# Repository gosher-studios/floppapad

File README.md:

silly little macropad

### features
- 10 hotswappable mx switches
- 128x32px oled display
- rotary encoder
- usb c
- scriptable and extensible firmware (coming soon)
- the silly caracal
<br/><br/><br/>

### Parts list

| Part                             | Quantity | Est. price | Example link |
|----------------------------------|----------|------------|--------------|
| RP2040                           | 1        | $1.01      | [LCSC](https://www.lcsc.com/product-detail/Microcontroller-Units-MCUs-MPUs-SOCs_Raspberry-Pi-RP2040_C2040.html) |
| USB-C port                       | 1        | $0.16      | [LCSC](https://www.lcsc.com/product-detail/USB-Connectors_Korean-Hroparts-Elec-TYPE-C-31-M-12_C165948.html) |
| SSD1306 128x32 OLED board        | 1        | $4.00      | [42. Keebs](https://42keebs.eu/shop/parts/oled-display-0-91-128x32) |
| EC11 Rotary encoder              | 1        | $2.00      | [LCSC](https://www.lcsc.com/product-detail/span-style-background-color-ff0-Rotary-span-Encoders_ALPSALPINE-EC11E183440C_C370986.html) |
| Kailh MX Hotswap sockets         | 10       | $3.00      | [Mechboards](https://mechboards.co.uk/collections/components/products/kailh-hotswap-sockets) |
| MX Compatible switches           | 10       | ~$10.00    | bring your favourite ✨ |
| SOIC 208-mil SPI flash[^1]       | 1        | $0.56      | [LCSC](https://www.lcsc.com/product-detail/NOR-FLASH_Winbond-Elec-W25Q128JVSIQ_C97521.html) |
| SMD3225 12MHz Crystal oscillator | 1        | $0.06      | [LCSC](https://www.lcsc.com/product-detail/Crystals_YXC-X322512MSB4SI_C9002.html) |
| 3.9x2.9mm SMD Switch             | 1        | $0.11      | [LCSC](https://www.lcsc.com/product-detail/Tactile-Switches_ALPSALPINE-SKRKAEE020_C115357.html) |
| SOT-89 3.3v Voltage regulator    | 1        | $0.05      | [LCSC](https://www.lcsc.com/product-detail/Linear-Voltage-Regulators-LDO_UMW-Youtai-Semiconductor-Co-Ltd-AMS1117-3-3_C347256.html) |
| 27.4Ω Resistors[^2]              | 2        | < $0.00    | [LCSC](https://www.lcsc.com/product-detail/Chip-Resistor-Surface-Mount_UNI-ROYAL-Uniroyal-Elec-0402WGF274JTCE_C31439.html) |
| 1kΩ Resistors[^2]                | 2        | < $0.00    | [LCSC](https://www.lcsc.com/product-detail/Chip-Resistor-Surface-Mount_UNI-ROYAL-Uniroyal-Elec-0402WGF1001TCE_C11702.html) |
| 5.1kΩ Resistors[^2]              | 2        | < $0.00    | [LCSC](https://www.lcsc.com/product-detail/Chip-Resistor-Surface-Mount_UNI-ROYAL-Uniroyal-Elec-0402WGF5101TCE_C25905.html) |
| 27pF Capacitors[^2]              | 2        | < $0.00    | [LCSC](https://www.lcsc.com/product-detail/Multilayer-Ceramic-Capacitors-MLCC-SMD-SMT_Samsung-Electro-Mechanics-CL05C270JB51PNC_C472451.html) |
| 100nF Capacitors[^2]             | 10       | < $0.00    | [LCSC](https://www.lcsc.com/product-detail/Multilayer-Ceramic-Capacitors-MLCC-SMD-SMT_Samsung-Electro-Mechanics-CL05B104KO5NNNC_C1525.html) |
| 1uF Capacitors[^2]               | 2        | < $0.00    | [LCSC](https://www.lcsc.com/product-detail/Multilayer-Ceramic-Capacitors-MLCC-SMD-SMT_Samsung-Electro-Mechanics-CL05A105KA5NQNC_C52923.html) |
| 10uF Capacitors[^2]              | 2        | < $0.00    | [LCSC](https://www.lcsc.com/product-detail/Multilayer-Ceramic-Capacitors-MLCC-SMD-SMT_Samsung-Electro-Mechanics-CL05A106MQ5NUNC_C15525.html) |

[^1]: The firmware is ~36KB for a release build. We use 16MB flash.
[^2]: All resistors and capacitors are 0402.

### Credits

Brought to you by Alex T and Gosha T ❤️ \
This work is licensed under [Creative Commons BY-NC-SA 4.0](https://creativecommons.org/licenses/by-nc-sa/4.0/)

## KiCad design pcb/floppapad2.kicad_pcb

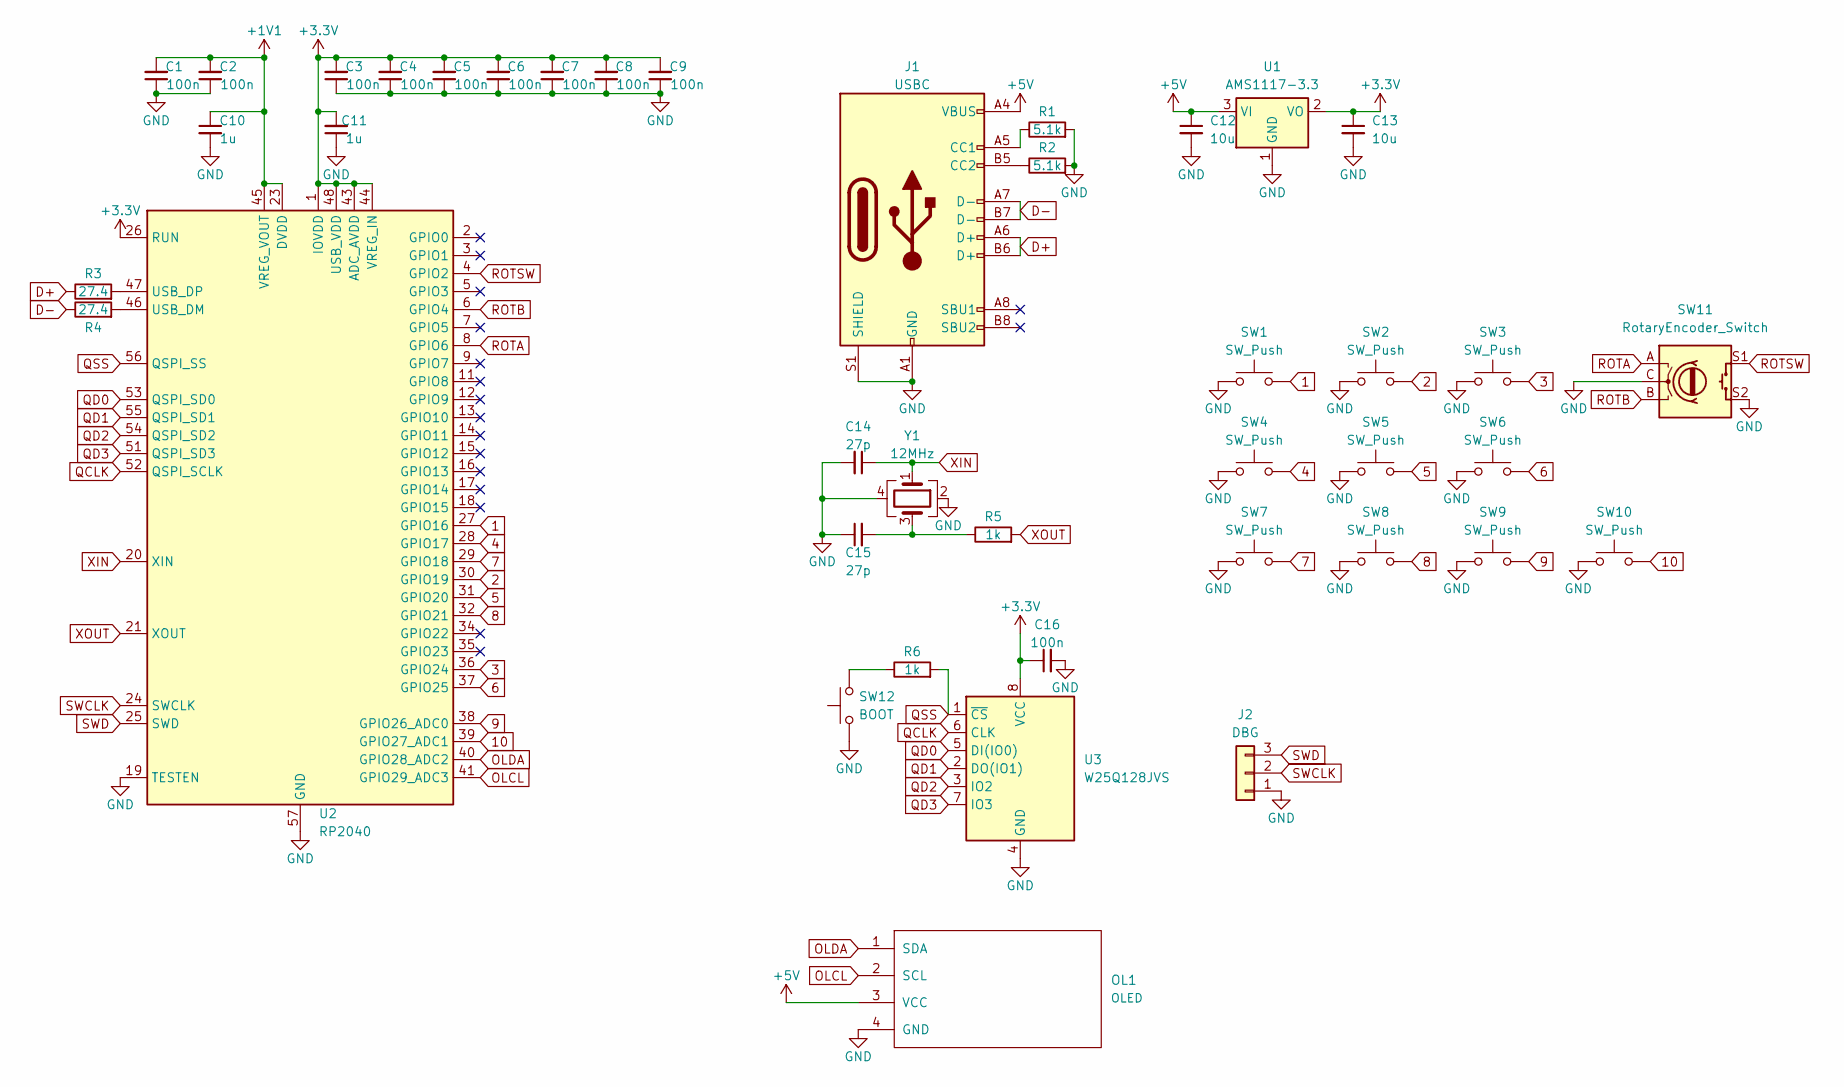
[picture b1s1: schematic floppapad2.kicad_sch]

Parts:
C1, C2, C3, C4, C5, C6, C7, C8, C9, C16: 100n; C_0402_1005Metric
C10, C11: 1u; C_0402_1005Metric
C12, C13: 10u; C_0402_1005Metric
C14, C15: 27p; C_0402_1005Metric
J1: USBC; USB_C_Receptacle_HRO_TYPE-C-31-M-12
J2: DBG; PinSocket_1x03_P2.54mm_Vertical
OL1: OLED; OLED_v2.1
R1, R2: 5.1k; R_0402_1005Metric
R3, R4: 27.4; R_0402_1005Metric
R5, R6: 1k; R_0402_1005Metric
SW1, SW2, SW3, SW4, SW5, SW6, SW7, SW8, SW9, SW10: SW_Push; SW_Hotswap_Kailh_MX_1.00u
SW11: RotaryEncoder_Switch; RotaryEncoder_Alps_EC11E-Switch_Vertical_H20mm
SW12: BOOT; SW_Push_SPST_NO_Alps_SKRK
U1: AMS1117-3.3; SOT-89-3
U2: RP2040; QFN-56-1EP_7x7mm_P0.4mm_EP3.2x3.2mm
U3: W25Q128JVS; SOIC-8_5.23x5.23mm_P1.27mm
Y1: 12MHz; Crystal_SMD_TXC_7M-4Pin_3.2x2.5mm

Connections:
1: SW1.2, U2.27 (GPIO16)
2: SW2.2, U2.30 (GPIO19)
3: SW3.2, U2.36 (GPIO24)
4: SW4.2, U2.28 (GPIO17)
5: SW5.2, U2.31 (GPIO20)
6: SW6.2, U2.37 (GPIO25)
7: SW7.2, U2.29 (GPIO18)
8: SW8.2, U2.32 (GPIO21)
9: SW9.2, U2.38 (GPIO26_ADC0)
10: SW10.2, U2.39 (GPIO27_ADC1)
+1V1: C1.2, C2.2, C10.1, U2.23 (DVDD), U2.45 (VREG_VOUT), U2.50 (DVDD)
+3.3V: C3.2, C4.2, C5.2, C6.2, C7.2, C8.2, C9.2, C11.2, C13.1, C16.1, U1.2 (VO), U2.1 (IOVDD), U2.10 (IOVDD), U2.22 (IOVDD), U2.26 (RUN), U2.33 (IOVDD), U2.42 (IOVDD), U2.43 (ADC_AVDD), U2.44 (VREG_IN), U2.48 (USB_VDD), U2.49 (IOVDD), U3.8 (VCC)
+5V: C12.1, J1.A4 (VBUS), J1.A9 (VBUS), J1.B4 (VBUS), J1.B9 (VBUS), OL1.3 (VCC), U1.3 (VI)
D+: J1.A6 (D+), J1.B6 (D+), R3.1
D-: J1.A7 (D-), J1.B7 (D-), R4.1
GND: C1.1, C2.1, C3.1, C4.1, C5.1, C6.1, C7.1, C8.1, C9.1, C10.2, C11.1, C12.2, C13.2, C14.2, C15.1, C16.2, J1.A1 (GND), J1.A12 (GND), J1.B1 (GND), J1.B12 (GND), J1.S1 (SHIELD), J2.1, OL1.4 (GND), R1.2, R2.2, SW1.1, SW2.1, SW3.1, SW4.1, SW5.1, SW6.1, SW7.1, SW8.1, SW9.1, SW10.1, SW11.C, SW11.S2, SW12.1, SW12.C, SW12.S2, U1.1 (GND), U2.19 (TESTEN), U2.57 (GND), U3.4 (GND), Y1.2, Y1.4; also elsewhere on the board
unnamed: C15.2, R5.1, Y1.3
unnamed: J1.A5 (CC1), R1.1
unnamed: J1.B5 (CC2), R2.1
unnamed: R6.1, SW12.2
unnamed: R4.2, U2.46 (USB_DM)
unnamed: R3.2, U2.47 (USB_DP)
OLCL: OL1.2 (SCL), U2.41 (GPIO29_ADC3)
OLDA: OL1.1 (SDA), U2.40 (GPIO28_ADC2)
QCLK: U2.52 (QSPI_SCLK), U3.6 (CLK)
QD0: U2.53 (QSPI_SD0), U3.5 (DI(IO0))
QD1: U2.55 (QSPI_SD1), U3.2 (DO(IO1))
QD2: U2.54 (QSPI_SD2), U3.3 (IO2)
QD3: U2.51 (QSPI_SD3), U3.7 (IO3)
QSS: R6.2, U2.56 (QSPI_SS), U3.1 (~CS)
ROTA: SW11.A, U2.8 (GPIO6)
ROTB: SW11.B, U2.6 (GPIO4)
ROTSW: SW11.S1, U2.4 (GPIO2)
SWCLK: J2.2, U2.24 (SWCLK); also elsewhere on the board
SWD: J2.3, U2.25 (SWD); also elsewhere on the board
XIN: C14.1, U2.20 (XIN), Y1.1
XOUT: R5.2, U2.21 (XOUT)

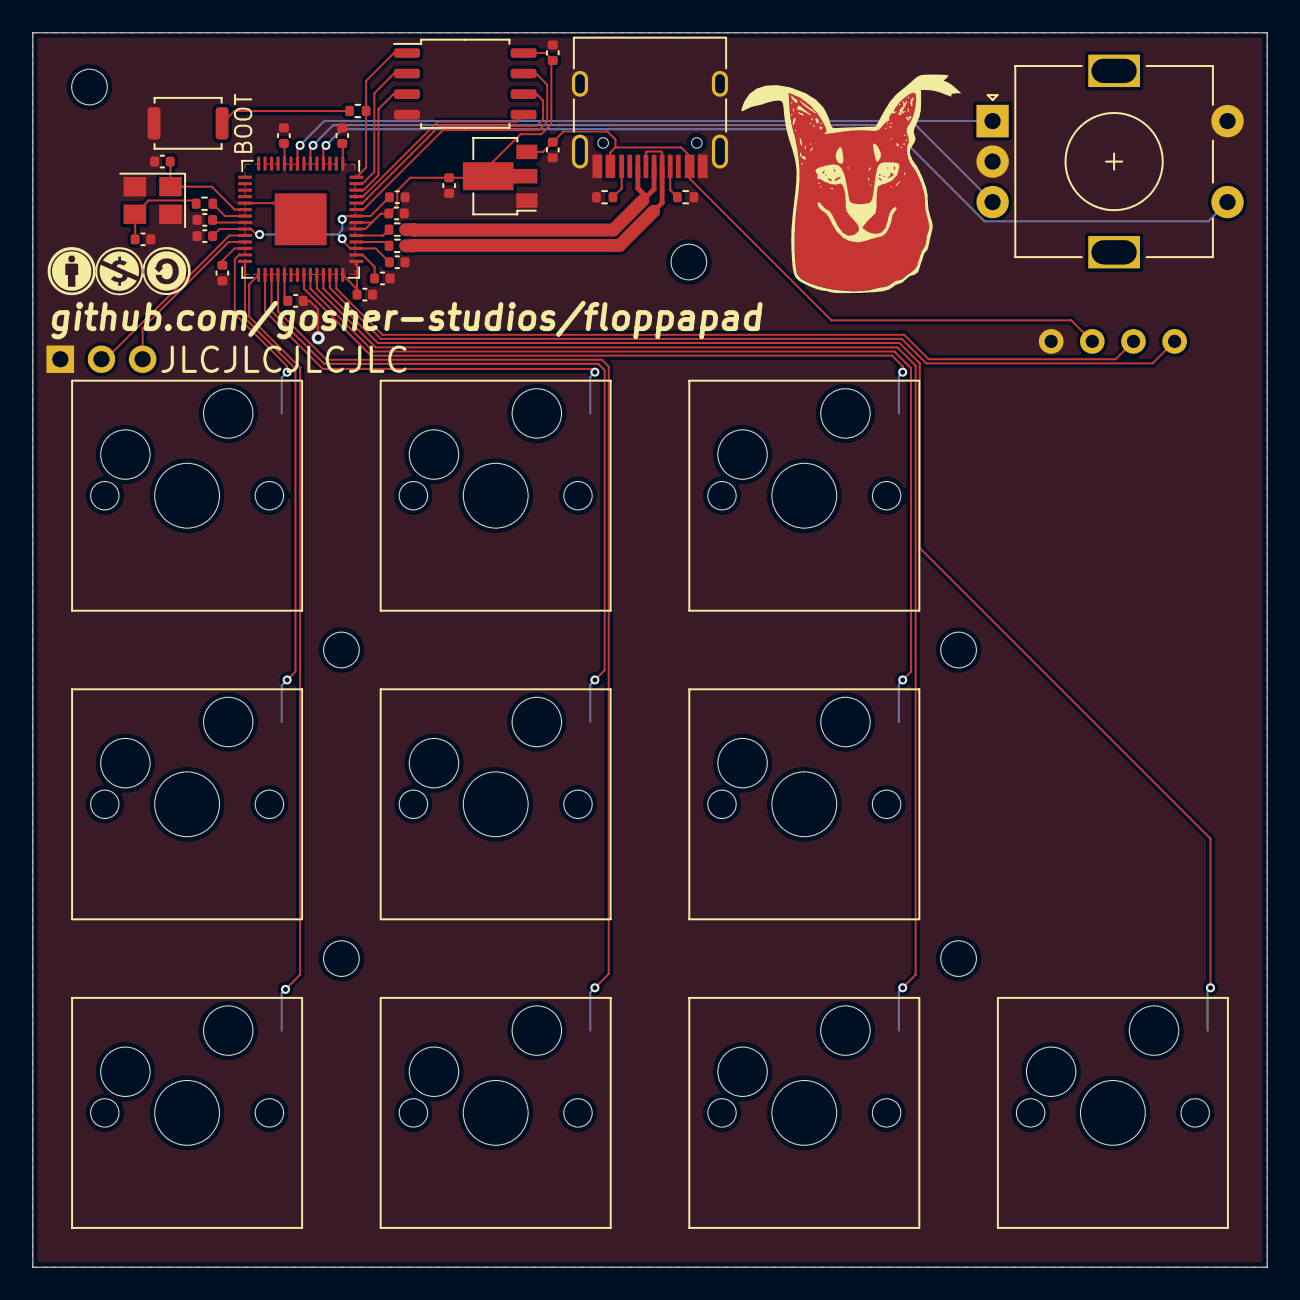
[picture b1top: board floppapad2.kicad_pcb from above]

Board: 2 copper layers, 76.2 x 76.2 mm, 41 parts (0 on the bottom side), 37 nets.

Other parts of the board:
DBG: DBG; PinSocket_1x03_P2.54mm_Vertical

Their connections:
GND: DBG.1; also elsewhere on the board
SWCLK: DBG.2; also elsewhere on the board
SWD: DBG.3; also elsewhere on the board

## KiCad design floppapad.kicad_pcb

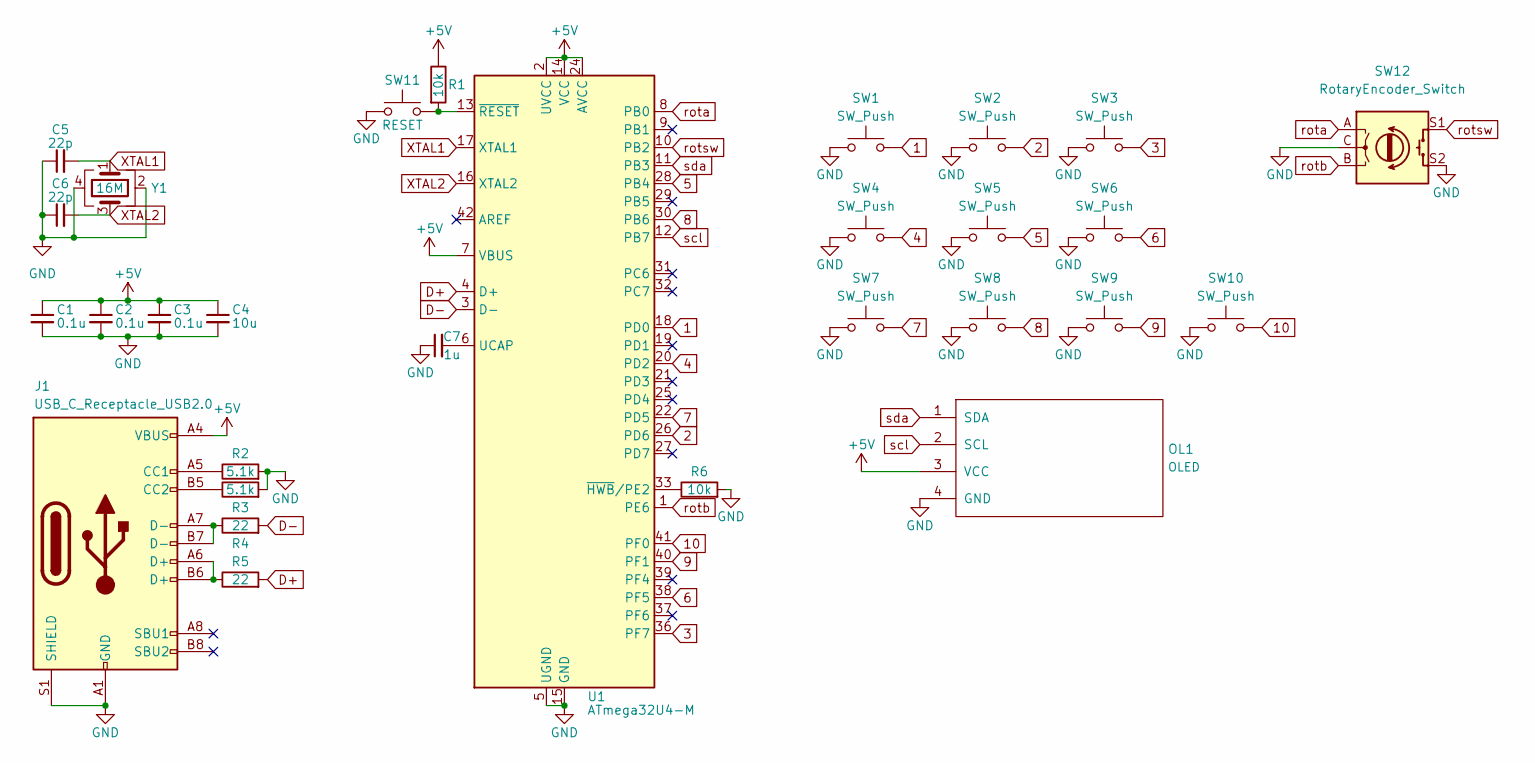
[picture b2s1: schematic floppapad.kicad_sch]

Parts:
C1, C2, C3: 0.1u; C_0805_2012Metric
C4: 10u; C_0805_2012Metric
C5, C6: 22p; C_0805_2012Metric
C7: 1u; C_0805_2012Metric
J1: USB_C_Receptacle_USB2.0; USB_C_Receptacle_XKB_U262-16XN-4BVC11
OL1: OLED; OLED_v2.1
R1, R6: 10k; R_0805_2012Metric
R2, R3: 5.1k; R_0805_2012Metric
R4, R5: 22; R_0805_2012Metric
SW1, SW2, SW3, SW4, SW5, SW6, SW7, SW8, SW9, SW10: SW_Push; SW_Hotswap_Kailh_MX_1.00u
SW11: RESET; SW_SPST_PTS645
SW12: RotaryEncoder_Switch; RotaryEncoder_Alps_EC11E-Switch_Vertical_H20mm
U1: ATmega32U4-M; QFN-44-1EP_7x7mm_P0.5mm_EP5.2x5.2mm
Y1: 16M; Crystal_SMD_3225-4Pin_3.2x2.5mm

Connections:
1: SW1.2, U1.18 (PD0)
2: SW2.2, U1.26 (PD6)
3: SW3.2, U1.36 (PF7)
4: SW4.2, U1.20 (PD2)
5: SW5.2, U1.28 (PB4)
6: SW6.2, U1.38 (PF5)
7: SW7.2, U1.22 (PD5)
8: SW8.2, U1.30 (PB6)
9: SW9.2, U1.40 (PF1)
10: SW10.2, U1.41 (PF0)
+5V: C1.1, C2.1, C3.1, C4.1, J1.A4 (VBUS), J1.A9 (VBUS), J1.B4 (VBUS), J1.B9 (VBUS), OL1.3 (VCC), R1.1, U1.2 (UVCC), U1.7 (VBUS), U1.14 (VCC), U1.24 (AVCC), U1.34 (VCC), U1.44 (AVCC)
D+: R5.2, U1.4 (D+)
D-: R4.2, U1.3 (D-)
GND: C1.2, C2.2, C3.2, C4.2, C5.1, C6.1, C7.1, J1.A1 (GND), J1.A12 (GND), J1.B1 (GND), J1.B12 (GND), J1.S1 (SHIELD), OL1.4 (GND), R2.2, R3.2, R6.2, SW1.1, SW2.1, SW3.1, SW4.1, SW5.1, SW6.1, SW7.1, SW8.1, SW9.1, SW10.1, SW11.1, SW12.C, SW12.S2, U1.5 (UGND), U1.15 (GND), U1.23 (GND), U1.35 (GND), U1.43 (GND), U1.45 (GND), Y1.2, Y1.4
unnamed: C7.2, U1.6 (UCAP)
unnamed: J1.A5 (CC1), R2.1
unnamed: J1.A6 (D+), J1.B6 (D+), R5.1
unnamed: J1.A7 (D-), J1.B7 (D-), R4.1
unnamed: J1.B5 (CC2), R3.1
unnamed: R1.2, SW11.2, U1.13 (~RESET)
unnamed: R6.1, U1.33 (~HWB/PE2)
XTAL1: C5.2, U1.17 (XTAL1), Y1.1
XTAL2: C6.2, U1.16 (XTAL2), Y1.3
rota: SW12.A, U1.8 (PB0)
rotb: SW12.B, U1.1 (PE6)
rotsw: SW12.S1, U1.10 (PB2)
scl: OL1.2 (SCL), U1.12 (PB7)
sda: OL1.1 (SDA), U1.11 (PB3)

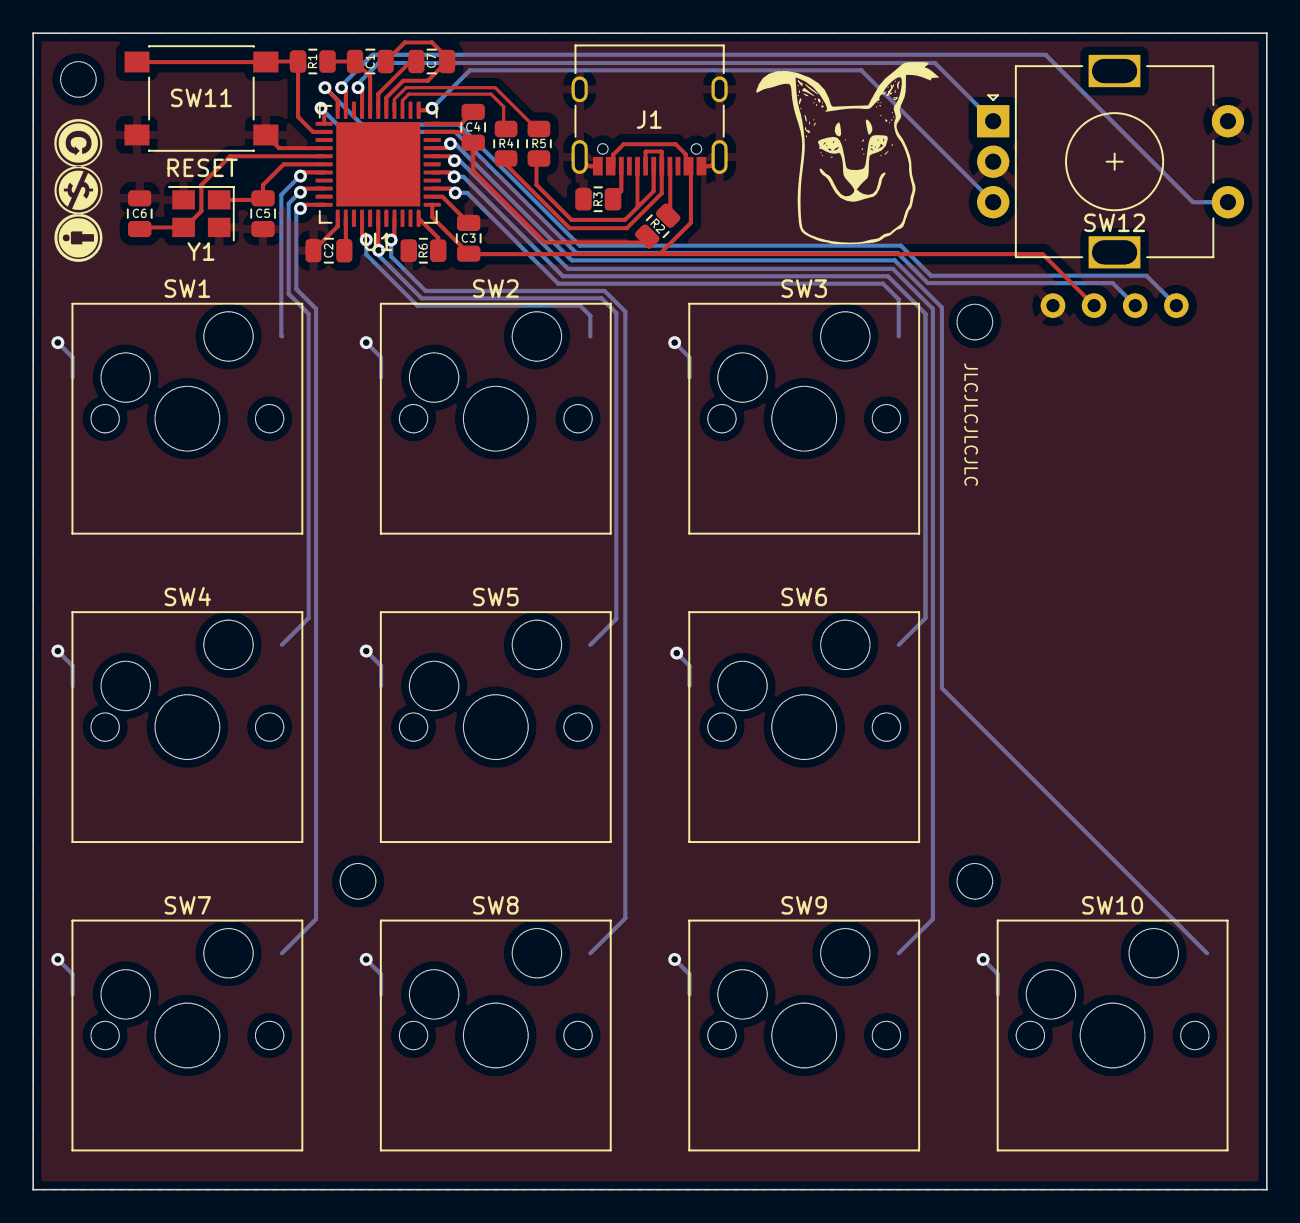
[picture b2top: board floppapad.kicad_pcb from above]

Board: 2 copper layers, 76.2 x 71.4 mm, 29 parts (0 on the bottom side), 28 nets.

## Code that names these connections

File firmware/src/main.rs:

#![no_std]
#![no_main]
extern crate alloc;

use core::str;
use core::fmt::Write;
use core::mem::MaybeUninit;
use alloc::string::String;
use alloc::vec::Vec;
use rp2040_hal::pac::Peripherals;
use rp2040_hal::watchdog::Watchdog;
use rp2040_hal::sio::Sio;
use rp2040_hal::clocks::{Clock, init_clocks_and_plls};
use rp2040_hal::timer::Timer;
use rp2040_hal::gpio::{DynPinId, FunctionSioInput, Pin, Pins, PullUp};
use rp2040_hal::i2c::I2C;
use rp2040_hal::usb::UsbBus;
use rp2040_hal::fugit::{ExtU32, RateExtU32};
use rp2040_flash::flash::flash_unique_id;
use cortex_m::interrupt;
use embedded_hal::prelude::*;
use embedded_hal::digital::v2::InputPin;
use embedded_hal::timer::CountDown;
use embedded_alloc::Heap;
use usb_device::{UsbError, UsbDirection, LangID};
use usb_device::bus::{UsbBusAllocator, InterfaceNumber};
use usb_device::device::{UsbDeviceBuilder, UsbVidPid, StringDescriptors};
use usb_device::descriptor::DescriptorWriter;
use usb_device::class::{UsbClass, ControlOut};
use usb_device::endpoint::{EndpointOut, EndpointAddress, EndpointType};
use usb_device::control::RequestType;
use usbd_hid::hid_class::HIDClass;
use usbd_hid::descriptor::{KeyboardReport, KeyboardUsage, SerializedDescriptor};
use ssd1306::{Ssd1306, I2CDisplayInterface};
use ssd1306::size::DisplaySize128x32;
use ssd1306::rotation::DisplayRotation;
use ssd1306::mode::DisplayConfig;
use rhai::{Engine, AST, Scope};
use rhai::packages::{Package, CorePackage};
use defmt::{info, debug, warn};
use floppapad_firmware::{ControlType, VENDOR_ID, VENDOR_NAME, PRODUCT_ID, PRODUCT_NAME, BULK_OUT_ADDR};

use defmt_rtt as _;
use panic_probe as _;

const XOSC_FREQ: u32 = 12_000_000;
const HEAP_SIZE: usize = 1024 * 128;

#[used]
#[link_section = ".boot2"]
static BOOT_LOADER: [u8; 256] = rp2040_boot2::BOOT_LOADER_W25Q080;
#[global_allocator]
static HEAP: Heap = Heap::empty();
static mut HEAP_MEM: [MaybeUninit<u8>; HEAP_SIZE] = [MaybeUninit::uninit(); HEAP_SIZE];

#[rp2040_hal::entry]
unsafe fn main() -> ! {
  info!("floppapad v2, firmware v{}", env!("CARGO_PKG_VERSION"));
  HEAP.init(HEAP_MEM.as_ptr() as _, HEAP_SIZE);
  let mut pac = Peripherals::take().unwrap();
  let mut watchdog = Watchdog::new(pac.WATCHDOG);
  let sio = Sio::new(pac.SIO);
  let clocks = init_clocks_and_plls(
    XOSC_FREQ,
    pac.XOSC,
    pac.CLOCKS,
    pac.PLL_SYS,
    pac.PLL_USB,
    &mut pac.RESETS,
    &mut watchdog,
  )
  .ok()
  .unwrap();
  let timer = Timer::new(pac.TIMER, &mut pac.RESETS, &clocks);

  let usb_bus = UsbBusAllocator::new(UsbBus::new(
    pac.USBCTRL_REGS,
    pac.USBCTRL_DPRAM,
    clocks.usb_clock,
    true,
    &mut pac.RESETS,
  ));
  let mut usb_control = ControlClass::new(&usb_bus);
  let mut usb_hid = HIDClass::new(&usb_bus, KeyboardReport::desc(), 60);
  let serial_number = get_serial_number();
  let version_bcd = get_version_bcd();
  let mut usb_dev = UsbDeviceBuilder::new(&usb_bus, UsbVidPid(VENDOR_ID, PRODUCT_ID))
    .strings(&[StringDescriptors::new(LangID::EN_US)
      .manufacturer(VENDOR_NAME)
      .product(PRODUCT_NAME)
      .serial_number(&serial_number)])
    .unwrap()
    .device_release(version_bcd)
    .build();

  // let pins = Pins::new(
  //   pac.IO_BANK0,
  //   pac.PADS_BANK0,
  //   sio.gpio_bank0,
  //   &mut pac.RESETS,
  // );
  // let mut keys: [Pin<DynPinId, FunctionSioInput, PullUp>; 10] = [
  //   pins.gpio16.into_pull_up_input().into_dyn_pin(), // top left
  //   pins.gpio17.into_pull_up_input().into_dyn_pin(), // middle left
  //   pins.gpio18.into_pull_up_input().into_dyn_pin(), // bottom left
  //   pins.gpio19.into_pull_up_input().into_dyn_pin(), // top middle
  //   pins.gpio20.into_pull_up_input().into_dyn_pin(), // middle middle
  //   pins.gpio21.into_pull_up_input().into_dyn_pin(), // bottom middle
  //   pins.gpio24.into_pull_up_input().into_dyn_pin(), // top right
  //   pins.gpio25.into_pull_up_input().into_dyn_pin(), // middle right
  //   pins.gpio26.into_pull_up_input().into_dyn_pin(), // bottom right
  //   pins.gpio27.into_pull_up_input().into_dyn_pin(), // sigma key TODO rename
  // ];

  // let oled_i2c = I2C::i2c0(
  //   pac.I2C0,
  //   pins.gpio28.into_function(),
  //   pins.gpio29.into_function(),
  //   400.kHz(),
  //   &mut pac.RESETS,
  //   clocks.system_clock.freq(),
  // );
  // let mut oled = Ssd1306::new(
  //   I2CDisplayInterface::new(oled_i2c),
  //   DisplaySize128x32,
  //   DisplayRotation::Rotate0,
  // )
  // .into_terminal_mode();
  // oled.init().unwrap();
  // oled.print_char('f').unwrap();

  let mut engine = Engine::new_raw();
  engine.set_max_strings_interned(1024);
  engine.on_print(|s| info!("rhai: {}", s));
  engine.on_debug(|s, _, _| debug!("rhai: {}", s));
  CorePackage::new().register_into_engine(&mut engine);
  let mut ast = AST::empty();
  let mut scope = Scope::new();

  watchdog.start(1.secs());
  let mut usb_tick = timer.count_down();
  usb_tick.start(1.millis());
  let mut input_tick = timer.count_down();
  input_tick.start(100.millis());
  loop {
    if input_tick.wait().is_ok() {
      match usb_hid.push_input(&KeyboardReport {
        modifier: 0,
        reserved: 0,
        leds: 0,
        // keycodes: [KeyboardUsage::KeyboardAa as _, 0, 0, 0, 0, 0],
        keycodes: [0; 6],
      }) {
        Ok(_) | Err(UsbError::WouldBlock) => {}
        Err(e) => panic!("usb hid error: {:?}", e),
      }
    }
    if usb_tick.wait().is_ok() {
      if usb_dev.poll(&mut [&mut usb_control, &mut usb_hid]) {
        if let Some(src) = usb_control.buf.take_if(|b| b.len() == b.capacity()) {
          match engine.compile(str::from_utf8(&src).unwrap()) {
            Ok(a) => {
              ast = a;
              engine.call_fn::<()>(&mut scope, &ast, "init", ()).unwrap();
            }
            Err(e) => warn!("compile error {}", defmt::Display2Format(&e)),
          }
        }
      }
    }
    watchdog.feed();
  }
}

struct ControlClass<'a> {
  interface: InterfaceNumber,
  bulk_out: EndpointOut<'a, UsbBus>,
  buf: Option<Vec<u8>>,
}

impl<'a> ControlClass<'a> {
  fn new(usb_bus: &'a UsbBusAllocator<UsbBus>) -> Self {
    Self {
      interface: usb_bus.interface(),
      bulk_out: usb_bus
        .alloc(
          Some(EndpointAddress::from_parts(
            BULK_OUT_ADDR as _,
            UsbDirection::Out,
          )),
          EndpointType::Bulk,
          64,
          0,
        )
        .unwrap(),
      buf: None,
    }
  }
}

impl UsbClass<UsbBus> for ControlClass<'_> {
  fn get_configuration_descriptors(&self, writer: &mut DescriptorWriter) -> usb_device::Result<()> {
    writer.interface(self.interface, 0xff, 0, 0)?;
    writer.endpoint(&self.bulk_out)?;
    Ok(())
  }

  fn control_out(&mut self, xfer: ControlOut<UsbBus>) {
    if xfer.request().request_type == RequestType::Vendor {
      match ControlType::from(xfer.request().request) {
        ControlType::PreScript => {
          let len = xfer.request().value;
          self.buf = Some(Vec::with_capacity(len as _));
          debug!("allocated {} for script", len);
          xfer.accept().unwrap();
        }
        ControlType::Test => {
          info!("test");
          xfer.accept().unwrap()
        }
        _ => xfer.reject().unwrap(),
      }
    }
  }

  fn endpoint_out(&mut self, address: EndpointAddress) {
    if self.bulk_out.address() == address {
      if let Some(buf) = &mut self.buf {
        let mut local = [0u8; 64];
        let len = self.bulk_out.read(&mut local).unwrap_or_default();
        if buf.len() + len <= buf.capacity() {
          buf.extend_from_slice(&local[..len]);
        }
        debug!("received {} for script", len);
      }
    }
  }
}

/// generated from flash unique id
fn get_serial_number() -> String {
  let mut buf = [0; 8];
  interrupt::free(|_| unsafe { flash_unique_id(&mut buf, true) });
  let mut str = String::with_capacity(16);
  write!(&mut str, "{:016X}", u64::from_ne_bytes(buf)).unwrap();
  str
}

/// 0xaabc - a is major, b is minor, c is patch
fn get_version_bcd() -> u16 {
  env!("CARGO_PKG_VERSION_MAJOR").parse::<u16>().unwrap() * 0x100
    + env!("CARGO_PKG_VERSION_MINOR").parse::<u16>().unwrap() * 0x10
    + env!("CARGO_PKG_VERSION_PATCH").parse::<u16>().unwrap()
}

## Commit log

2023-12-11 slight adjustment
2023-12-11 clean
2023-12-11 mounting holes
2023-12-11 better debug
2023-12-11 exposed copper
2023-12-13 i <3 embedded rust
2023-12-18 cook
2023-12-19 defmt
2023-12-30 config
2023-12-30 oopsie :3
2023-12-31 dioxus silly
2024-07-05 i wrote an amount of code idk
2024-07-05 theoretically works
2024-07-11 write the reader
2024-07-11 minor readme
2024-07-12 readm
2024-07-12 specify res/cap package
2024-07-25 i am falling, i am fading, i am drowning
2024-07-30 code does stuff

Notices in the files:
README.md:
cc-by-nc-sa
